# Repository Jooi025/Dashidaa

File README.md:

# Dashidaa
Meet Dashidaa, the robot car companion with a face and a personality! It smiles, blinks, and reacts as you drive. With a rechargeable battery and a smart power system, Dashidaa keeps itself charged and ready for your adventure.
## PCB

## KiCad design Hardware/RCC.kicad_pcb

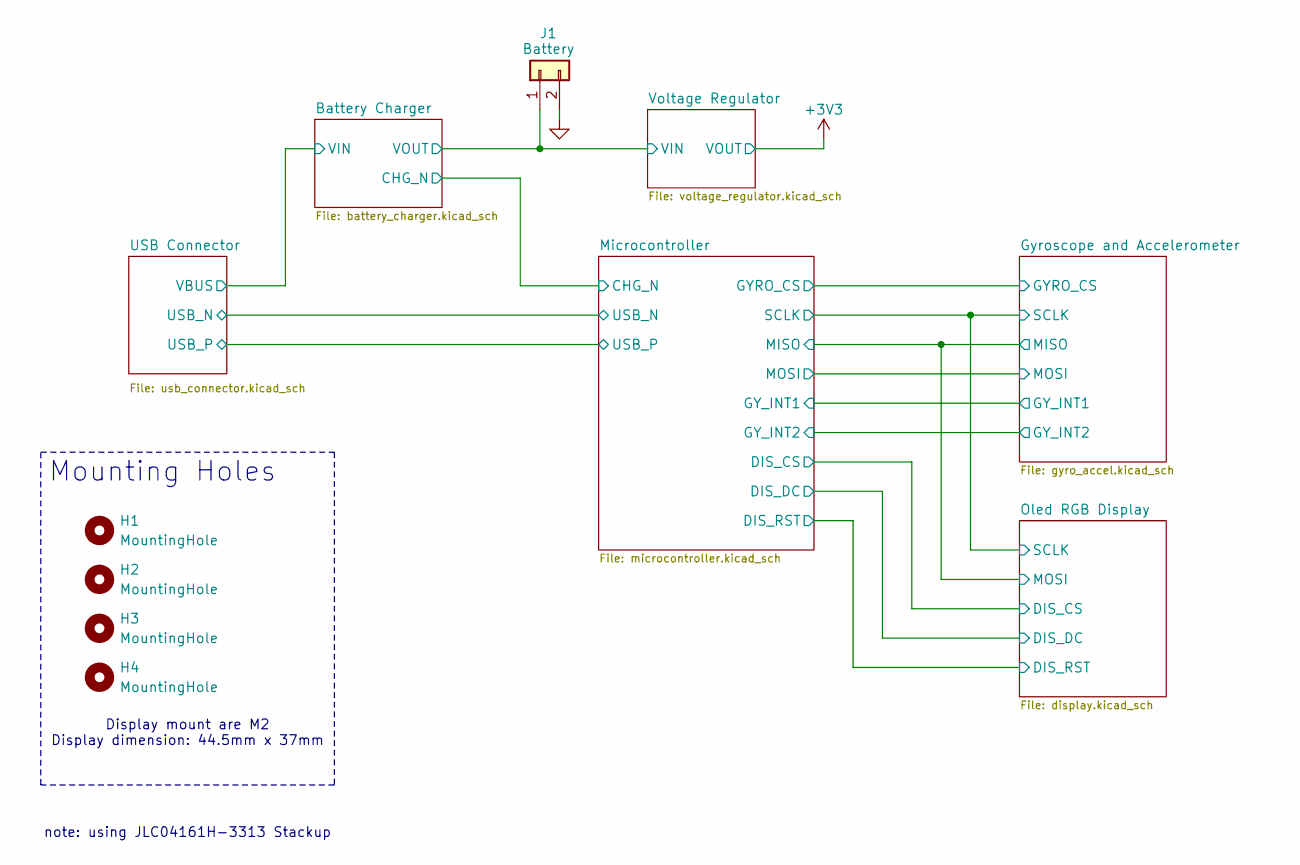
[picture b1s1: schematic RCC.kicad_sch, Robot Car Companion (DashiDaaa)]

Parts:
H1, H2, H3, H4: MountingHole; MountingHole_2.2mm_M2
J1: Battery; JST_PH_S2B-PH-K_1x02_P2.00mm_Horizontal

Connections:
/Battery Charger/VOUT: J1.1; also elsewhere on the board
GND: J1.2; also elsewhere on the board

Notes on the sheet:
Display mount are M2 Display dimension: 44.5mm x 37mm
note: using JLC04161H-3313 Stackup
Mounting Holes

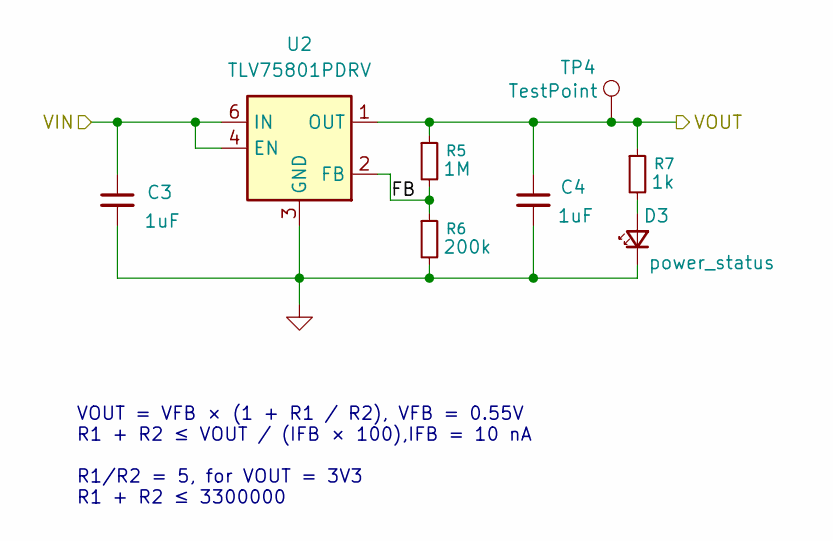
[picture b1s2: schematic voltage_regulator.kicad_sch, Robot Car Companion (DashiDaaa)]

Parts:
C3, C4: 1uF; C_0603_1608Metric_Pad1.08x0.95mm_HandSolder
D3: power_status; LED_0603_1608Metric_Pad1.05x0.95mm_HandSolder
R5: 1M; R_0603_1608Metric_Pad0.98x0.95mm_HandSolder
R6: 200k; R_0603_1608Metric_Pad0.98x0.95mm_HandSolder
R7: 1k; R_0603_1608Metric_Pad0.98x0.95mm_HandSolder
TP4: TestPoint; TestPoint_Pad_D1.0mm
U2: TLV75801PDRV; WSON-6-1EP_2x2mm_P0.65mm_EP1x1.6mm

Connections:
+3V3: C4.1, R5.1, R7.1, TP4.1, U2.1 (OUT); also elsewhere on the board
/Battery Charger/VOUT: C3.1, U2.4 (EN), U2.6 (IN); also elsewhere on the board
/Voltage Regulator/FB: R5.2, R6.1, U2.2 (FB)
GND: C3.2, C4.2, D3.1 (K), R6.2, U2.3 (GND), U2.7 (GND); also elsewhere on the board
unnamed: D3.2 (A), R7.2

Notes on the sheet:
VOUT = VFB × (1 + R1 / R2), VFB = 0.55V R1 + R2 ≤ VOUT / (IFB × 100),IFB = 10 nA R1/R2 = 5, for VOUT = 3V3 R1 + R2 ≤ 3300000

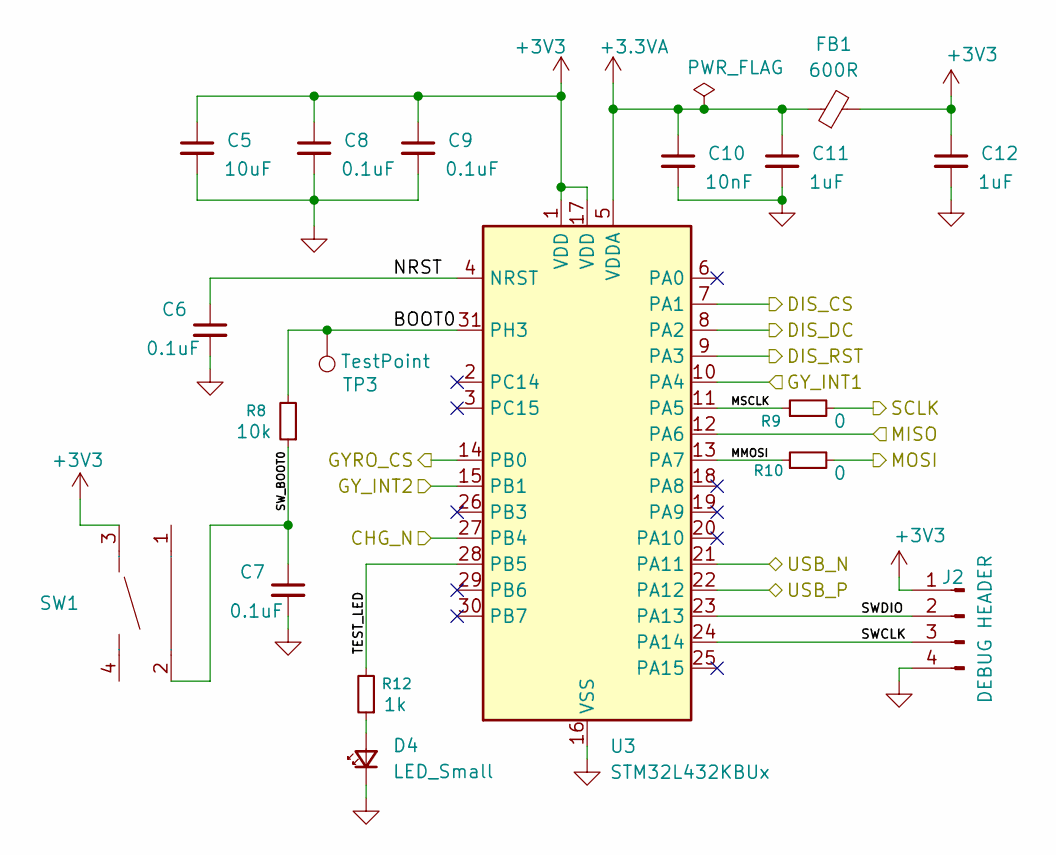
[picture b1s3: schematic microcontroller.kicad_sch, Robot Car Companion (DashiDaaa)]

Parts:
C5: 10uF; C_0603_1608Metric_Pad1.08x0.95mm_HandSolder
C6, C7, C8, C9: 0.1uF; C_0402_1005Metric_Pad0.74x0.62mm_HandSolder
C10: 10nF; C_0603_1608Metric_Pad1.08x0.95mm_HandSolder
C11, C12: 1uF; C_0603_1608Metric_Pad1.08x0.95mm_HandSolder
D4: LED_Small; LED_0603_1608Metric_Pad1.05x0.95mm_HandSolder
FB1: 600R; L_0603_1608Metric_Pad1.05x0.95mm_HandSolder
J2: DEBUG HEADER; JST_PH_S4B-PH-K_1x04_P2.00mm_Horizontal
R8: 10k; R_0603_1608Metric_Pad0.98x0.95mm_HandSolder
R9, R10: 0; R_0603_1608Metric_Pad0.98x0.95mm_HandSolder
R12: 1k; R_0603_1608Metric_Pad0.98x0.95mm_HandSolder
SW1: SW-SMD_TS24CA; Manufacturer Part TS24CA; LCSC Part Name 4.55*1.8*3.5mm 卧贴 轻触开关
TP3: TestPoint; TestPoint_Pad_D1.0mm
U3: STM32L432KBUx; QFN-32-1EP_5x5mm_P0.5mm_EP3.45x3.45mm

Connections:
+3.3VA: C10.1, C11.1, FB1.1, U3.5 (VDDA)
+3V3: C5.1, C8.1, C9.1, C12.1, FB1.2, J2.1, SW1.3, U3.1 (VDD), U3.17 (VDD); also elsewhere on the board
/Battery Charger/CHG_N: U3.27 (PB4); also elsewhere on the board
/Gyroscope and Accelerometer/GYRO_CS: U3.14 (PB0); also elsewhere on the board
/Gyroscope and Accelerometer/GY_INT1: U3.10 (PA4); also elsewhere on the board
/Gyroscope and Accelerometer/GY_INT2: U3.15 (PB1); also elsewhere on the board
/Gyroscope and Accelerometer/MISO: U3.12 (PA6); also elsewhere on the board
/Gyroscope and Accelerometer/MOSI: R10.2; also elsewhere on the board
/Gyroscope and Accelerometer/SCLK: R9.2; also elsewhere on the board
/Microcontroller/BOOT0: R8.2, TP3.1, U3.31 (PH3)
/Microcontroller/DIS_CS: U3.7 (PA1); also elsewhere on the board
/Microcontroller/DIS_DC: U3.8 (PA2); also elsewhere on the board
/Microcontroller/DIS_RST: U3.9 (PA3); also elsewhere on the board
/Microcontroller/MMOSI: R10.1, U3.13 (PA7)
/Microcontroller/MSCLK: R9.1, U3.11 (PA5)
/Microcontroller/NRST: C6.1, U3.4 (NRST)
/Microcontroller/SWCLK: J2.3, U3.24 (PA14)
/Microcontroller/SWDIO: J2.2, U3.23 (PA13)
/Microcontroller/SW_BOOT0: C7.1, R8.1, SW1.2
/Microcontroller/TEST_LED: R12.2, U3.28 (PB5)
/USB Connector/USB_N: U3.21 (PA11); also elsewhere on the board
/USB Connector/USB_P: U3.22 (PA12); also elsewhere on the board
GND: C5.2, C6.2, C7.2, C8.2, C9.2, C10.2, C11.2, C12.2, D4.1 (K), J2.4, U3.16 (VSS), U3.32 (VSS), U3.33 (VSS); also elsewhere on the board
unnamed: D4.2 (A), R12.1

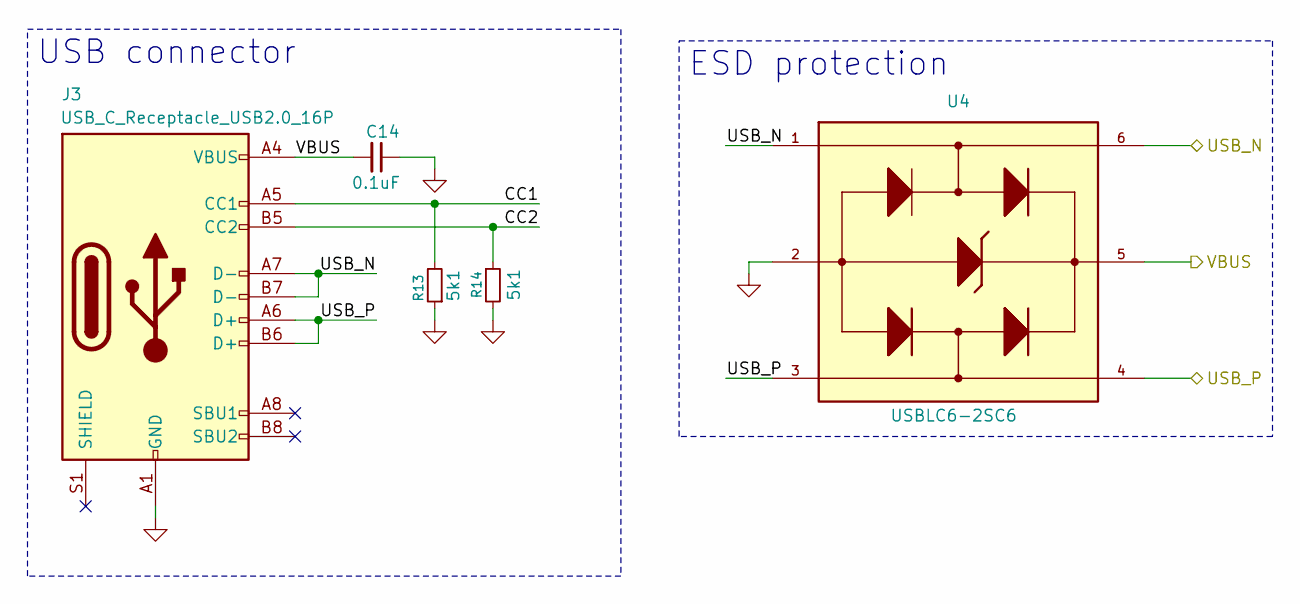
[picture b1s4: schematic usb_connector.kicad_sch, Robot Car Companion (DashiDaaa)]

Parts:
C14: 0.1uF; C_0603_1608Metric_Pad1.08x0.95mm_HandSolder
J3: USB_C_Receptacle_USB2.0_16P; USB_C_Receptacle_G-Switch_GT-USB-7010ASV
R13, R14: 5k1; R_0603_1608Metric_Pad0.98x0.95mm_HandSolder
U4: USBLC6-2SC6; SOT95P280X145-6N

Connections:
/USB Connector/CC1: J3.A5 (CC1), R13.2
/USB Connector/CC2: J3.B5 (CC2), R14.1
/USB Connector/USB_N: J3.A7 (D-), J3.B7 (D-), U4.1, U4.6; also elsewhere on the board
/USB Connector/USB_P: J3.A6 (D+), J3.B6 (D+), U4.3, U4.4; also elsewhere on the board
/USB Connector/VBUS: C14.2, J3.A4 (VBUS), J3.A9 (VBUS), J3.B4 (VBUS), J3.B9 (VBUS), U4.5; also elsewhere on the board
GND: C14.1, J3.A1 (GND), J3.A12 (GND), J3.B1 (GND), J3.B12 (GND), R13.1, R14.2, U4.2; also elsewhere on the board

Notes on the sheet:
ESD protection
USB connector

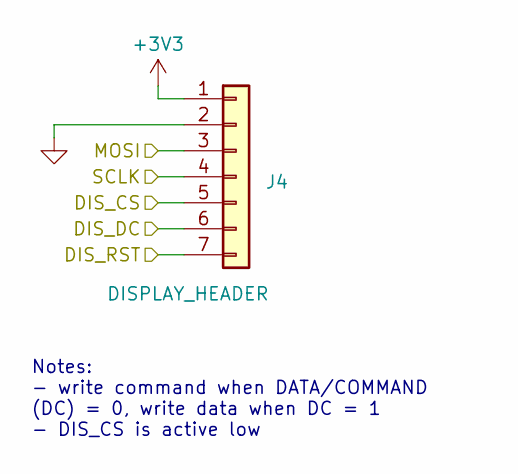
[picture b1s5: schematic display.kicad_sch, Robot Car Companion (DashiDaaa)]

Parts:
J4: DISPLAY_HEADER; PinSocket_1x07_P2.54mm_Vertical

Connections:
+3V3: J4.1; also elsewhere on the board
/Gyroscope and Accelerometer/MISO: J4.3; also elsewhere on the board
/Gyroscope and Accelerometer/SCLK: J4.4; also elsewhere on the board
/Microcontroller/DIS_CS: J4.5; also elsewhere on the board
/Microcontroller/DIS_DC: J4.6; also elsewhere on the board
/Microcontroller/DIS_RST: J4.7; also elsewhere on the board
GND: J4.2; also elsewhere on the board

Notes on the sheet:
Notes: - write command when DATA/COMMAND (DC) = 0, write data when DC = 1 - DIS_CS is active low

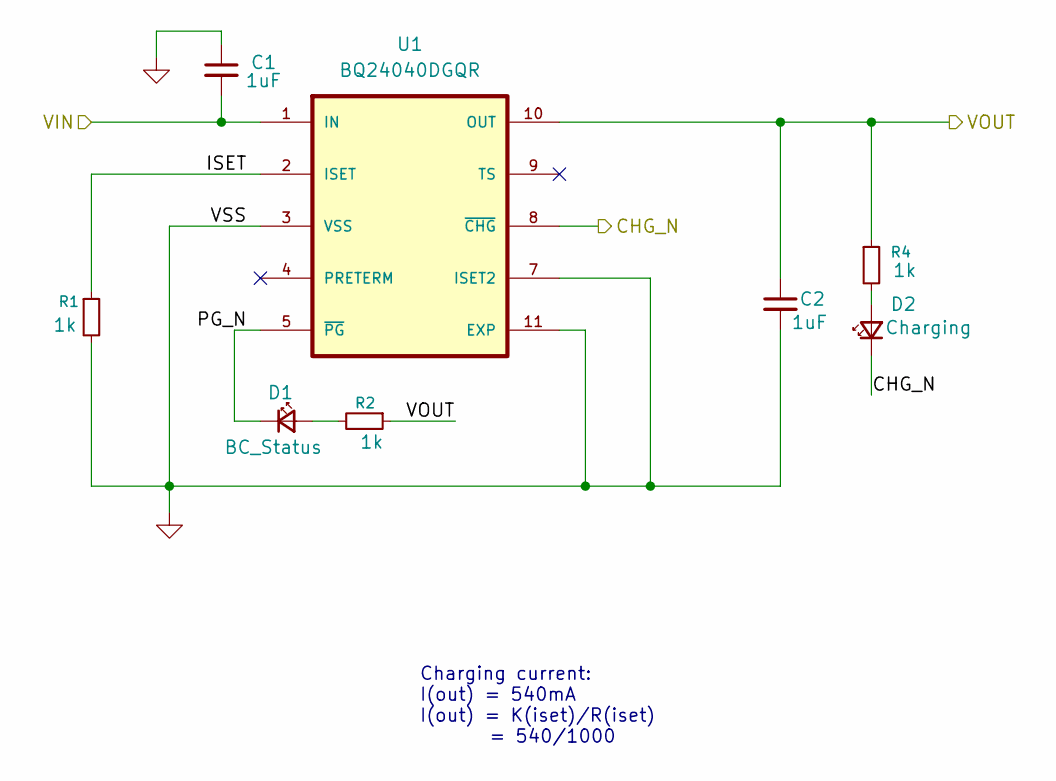
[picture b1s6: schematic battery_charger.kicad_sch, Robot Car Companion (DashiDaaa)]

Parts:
C1, C2: 1uF; C_0603_1608Metric_Pad1.08x0.95mm_HandSolder
D1: BC_Status; LED_0603_1608Metric_Pad1.05x0.95mm_HandSolder
D2: Charging; LED_0603_1608Metric_Pad1.05x0.95mm_HandSolder
R1, R2, R4: 1k; R_0603_1608Metric_Pad0.98x0.95mm_HandSolder
U1: BQ24040DGQR; SON40P200X200X80-11N

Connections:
/Battery Charger/CHG_N: D2.1 (K), U1.8 (~CHG); also elsewhere on the board
/Battery Charger/ISET: R1.1, U1.2 (ISET)
/Battery Charger/PG_N: D1.1 (K), U1.5 (~PG)
/Battery Charger/VOUT: C2.1, R2.1, R4.1, U1.10 (OUT); also elsewhere on the board
/USB Connector/VBUS: C1.2, U1.1 (IN); also elsewhere on the board
GND: C1.1, C2.2, R1.2, U1.3 (VSS), U1.7 (ISET2), U1.11 (EXP); also elsewhere on the board
unnamed: D1.2 (A), R2.2
unnamed: D2.2 (A), R4.2

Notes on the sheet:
Charging current: I(out) = 540mA I(out) = K(iset)/R(iset) = 540/1000

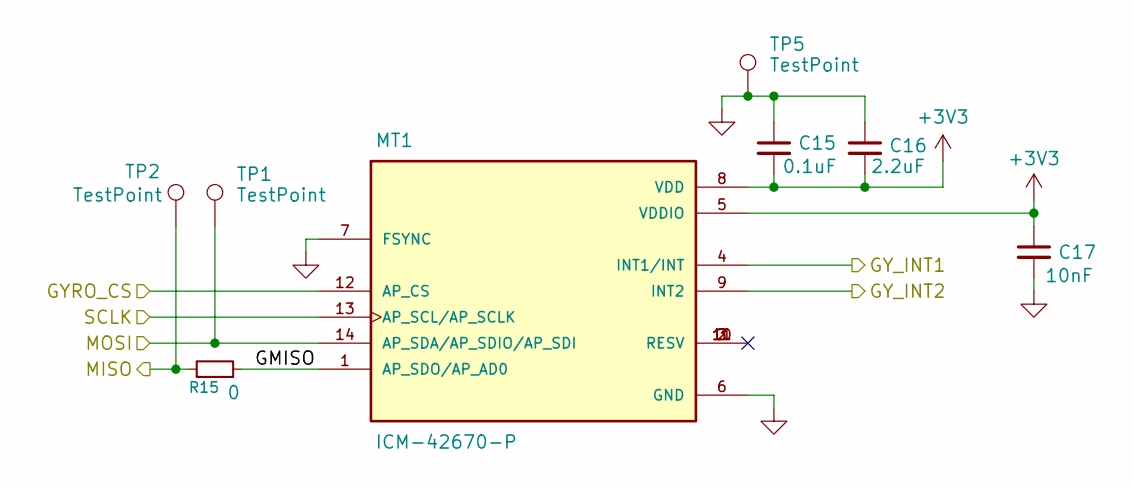
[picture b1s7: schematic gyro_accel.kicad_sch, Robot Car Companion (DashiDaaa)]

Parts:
C15: 0.1uF; C_0603_1608Metric_Pad1.08x0.95mm_HandSolder
C16: 2.2uF; C_0603_1608Metric_Pad1.08x0.95mm_HandSolder
C17: 10nF; C_0603_1608Metric_Pad1.08x0.95mm_HandSolder
MT1: ICM-42670-P; XDCR_ICM-42670-P; PARTREV 1.1
R15: 0; R_0603_1608Metric_Pad0.98x0.95mm_HandSolder
TP1, TP2, TP5: TestPoint; TestPoint_Pad_D1.0mm

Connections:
+3V3: C15.2, C16.2, C17.1, MT1.5 (VDDIO), MT1.8 (VDD); also elsewhere on the board
/Gyroscope and Accelerometer/GMISO: MT1.1 (AP_SDO/AP_AD0), R15.2
/Gyroscope and Accelerometer/GYRO_CS: MT1.12 (AP_CS); also elsewhere on the board
/Gyroscope and Accelerometer/GY_INT1: MT1.4 (INT1/INT); also elsewhere on the board
/Gyroscope and Accelerometer/GY_INT2: MT1.9 (INT2); also elsewhere on the board
/Gyroscope and Accelerometer/MISO: R15.1, TP2.1; also elsewhere on the board
/Gyroscope and Accelerometer/MOSI: MT1.14 (AP_SDA/AP_SDIO/AP_SDI), TP1.1; also elsewhere on the board
/Gyroscope and Accelerometer/SCLK: MT1.13 (AP_SCL/AP_SCLK); also elsewhere on the board
GND: C15.1, C16.1, C17.2, MT1.6 (GND), MT1.7 (FSYNC), TP5.1; also elsewhere on the board

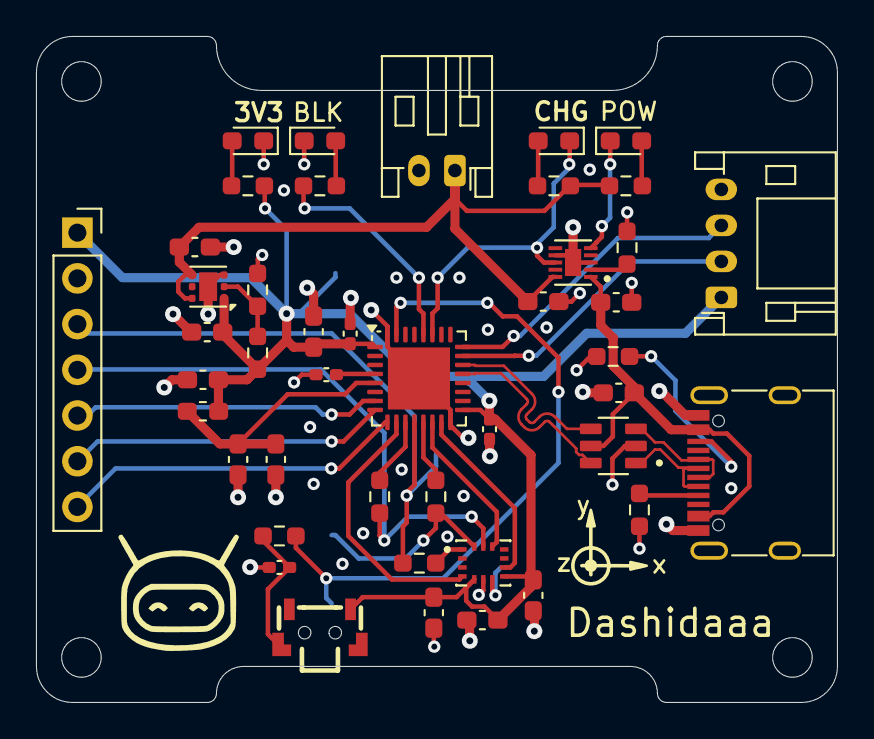
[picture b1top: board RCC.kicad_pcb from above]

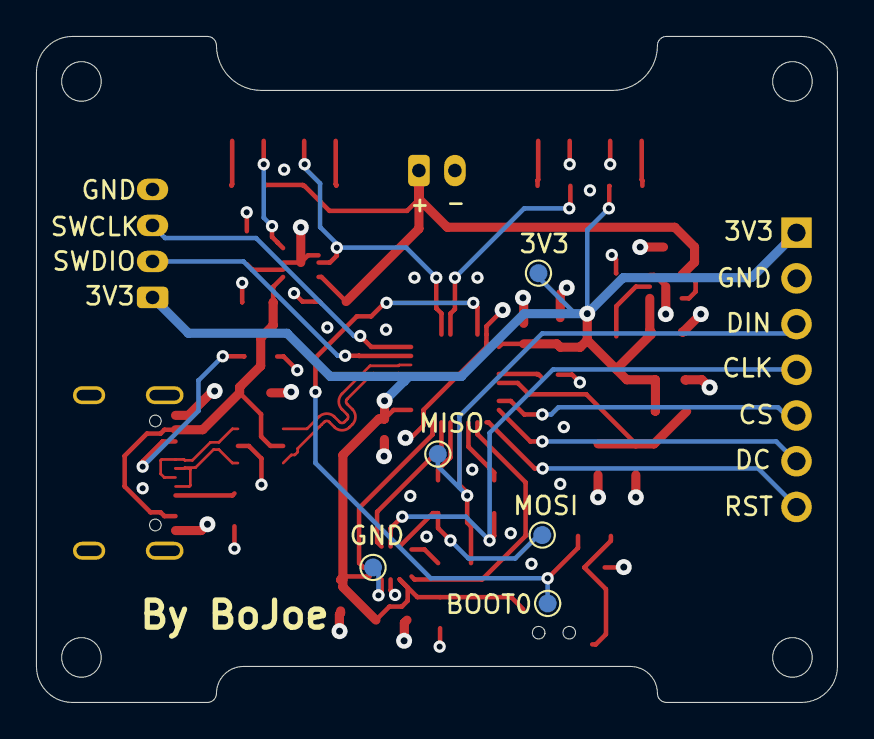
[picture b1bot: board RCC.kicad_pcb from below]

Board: 4 copper layers, 44.5 x 37.0 mm, 53 parts (5 on the bottom side), 35 nets.

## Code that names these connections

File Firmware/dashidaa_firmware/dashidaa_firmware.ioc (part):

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Mcu.Name=STM32L432K(B-C)Ux
Mcu.Package=UFQFPN32
Mcu.UserName=STM32L432KBUx
PA1.GPIOParameters=GPIO_Label
PA1.GPIO_Label=DIS_CS
PA1.Signal=GPIO_Output
PA11.Mode=Device
PA11.Signal=USB_DM
PA12.Mode=Device
PA12.Signal=USB_DP
PA13\ (JTMS-SWDIO).Mode=Serial_Wire
PA13\ (JTMS-SWDIO).Signal=SYS_JTMS-SWDIO
PA14\ (JTCK-SWCLK).Mode=Serial_Wire
PA14\ (JTCK-SWCLK).Signal=SYS_JTCK-SWCLK
PA2.GPIOParameters=GPIO_Label
PA2.GPIO_Label=DIS_DC
PA2.Signal=GPIO_Output
PA3.GPIOParameters=GPIO_Label
PA3.GPIO_Label=DIS_RST
PA3.Signal=GPIO_Output
PA4.GPIOParameters=GPIO_Label
PA4.GPIO_Label=GY_INT1
PA4.Signal=GPXTI4
PA5.Mode=Full_Duplex_Master
PA5.Signal=SPI1_SCK
PA6.Mode=Full_Duplex_Master
PA6.Signal=SPI1_MISO
PA7.Mode=Full_Duplex_Master
PA7.Signal=SPI1_MOSI
PB0.GPIOParameters=GPIO_Label
PB0.GPIO_Label=GY_CS
PB0.Signal=GPIO_Output
PB1.GPIOParameters=GPIO_Label
PB1.GPIO_Label=GY_INT2
PB1.Signal=GPXTI1
PB4\ (NJTRST).GPIOParameters=GPIO_Label
PB4\ (NJTRST).GPIO_Label=nCHG
PB4\ (NJTRST).Signal=GPIO_Input
PB5.GPIOParameters=GPIO_Label
PB5.GPIO_Label=BLINKY
PB5.Signal=GPIO_Output
RCC.HSE_VALUE=8000000
RCC.SYSCLKFreq_VALUE=32000000
RCC.SYSCLKSource=RCC_SYSCLKSOURCE_PLLCLK
board=custom

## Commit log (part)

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2025-05-31 Upload KiCad project
2025-05-31 Add microcontroller and display to schematic
2025-06-01 Add resistor value for regulator and pull up resistor and debug connector for microcontroller
2025-06-04 Initial PCB layout
2025-06-05 Change PCB stackup to 4 layer
2025-06-05 Add crystal in schematic and pcb
2025-06-06 Finalise PCB and add 3d models
2025-06-06 Change connectors to jst-ph
2025-06-06 Add PCB image
2025-06-07 Clean up pcb traces and vias
2025-06-10 Add termination resistor to spi and change esd protection
2025-06-20 Restructure folder and start revB
2025-07-02 Finish routing revB
2025-07-02 Add multiple page of schematic
2025-07-02 Add silkscreen to pcb
2025-07-05 Finnish RevB
2025-07-05 Add revB pcb image
2025-08-07 Add SVG for stencil
2025-10-17 Restructure folders
2026-01-29 Add gitignore
2026-01-29 Add STM32 code and helper python code
